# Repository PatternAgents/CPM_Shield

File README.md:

CPM Shield Adaptor
====================

PatternAgents CPM Shield Adaptor

[  
*PatternAgents CPM Shield Adaptor*](http://www.patternagents.com/projects/CPM_Shield.html)

The "CPM Shield Adaptor" board is designed to enable Cypress PSoC development boards to utilize Arduino Shield peripherals.

The PatternAgents "CPM Shield Adaptor" board supports :

Cypress CY8CKIT-001 : (Supports up to three (3) "CPM Shield Adaptor")

Cypress CY8CKIT-030 : (Supports up to two (2) "CPM Shield Adaptor")

Cypress CY8CKIT-050 : (Supports up to two (2) "CPM Shield Adaptor")

Cypress CY3280-28xxx : (Supports one (1) "CPM Shield Adaptor")

Cypress CY3280-22x45 : (Supports one (1) "CPM Shield Adaptor")

(Not an Exhaustive list as more Cypress development boards are routinely released)

For information on the Arduino Shield Specification, see http://www.arduino.cc

[  
*Licensing CC BY-NC-SA 4.0*](http://creativecommons.org/licenses/by-nc-sa/4.0/)

PatternAgents uses the increasingly popular business model called "Dual Licensing" 
in which both the open source software distribution mechanism and traditional commercial software distribution models are combined.

Open Source Projects:        

If you are developing and distributing open source applications under the Creative Commons CC BY-NC-SA 4.0, 
as published by the Creative Commons Foundation, then you are free to use the PatternAgents hardware/software under the CC BY-NC-SA 4.0 license. 
Please note that CC BY-NC-SA 4.0 requires that all modifications to the original code as well as all Derivative Works 
must also be released under the terms of the CC BY-NC-SA 4.0 license.

Closed Source Projects:

If you are developing and distributing traditional closed source or commercial applications, 
you must purchase a PatternAgents commercial use license, 
which is specifically designed for users interested in retaining the proprietary status of their designs and code. 
All PatternAgents commercial licenses expressly supersede the CC BY-NC-SA 4.0 license. 
This means that when you license the PatternAgents software under a commercial license, 
you specifically do not use the software under the CC BY-NC-SA 4.0 license and therefore you are not subject to any of its terms.
        
If you would like to use our designs for your own personal or educational use, have at it! 

Our public design repository is available at <a href="https://github.com/patternagents">Github</a>.

If you would like to produce our designs for commercial use, or as products for sale, 
please contact us to arrange for a Commercial Use license. We have many other designs, 
as well as options and extras that are not released publicly. 
We will also customize designs, firmware, and software for a reasonable fee, just contact us to discuss your requirements.

THIS SOFTWARE IS PROVIDED BY THE CONTRIBUTORS "AS IS" AND WITHOUT ANY EXPRESS OR IMPLIED WARRANTIES, 
INCLUDING, BUT NOT LIMITED TO, THE IMPLIED WARRANTIES OF MERCHANTABILITY AND FITNESS FOR A PARTICULAR PURPOSE ARE DISCLAIMED. 
IN NO EVENT SHALL THE COPYRIGHT OWNER OR CONTRIBUTORS BE LIABLE FOR ANY DIRECT, INDIRECT, INCIDENTAL, SPECIAL, EXEMPLARY, 
OR CONSEQUENTIAL DAMAGES (INCLUDING, BUT NOT LIMITED TO, PROCUREMENT OF SUBSTITUTE GOODS OR SERVICES; LOSS OF USE, DATA, 
OR PROFITS; OR BUSINESS INTERRUPTION) HOWEVER CAUSED AND ON ANY THEORY OF LIABILITY, WHETHER IN CONTRACT, 
STRICT LIABILITY, OR TORT (INCLUDING NEGLIGENCE OR OTHERWISE) ARISING IN ANY WAY OUT OF THE USE OF THIS SOFTWARE, 
EVEN IF ADVISED OF THE POSSIBILITY OF SUCH DAMAGE. 

-------------------------------------------------------------------------------------------

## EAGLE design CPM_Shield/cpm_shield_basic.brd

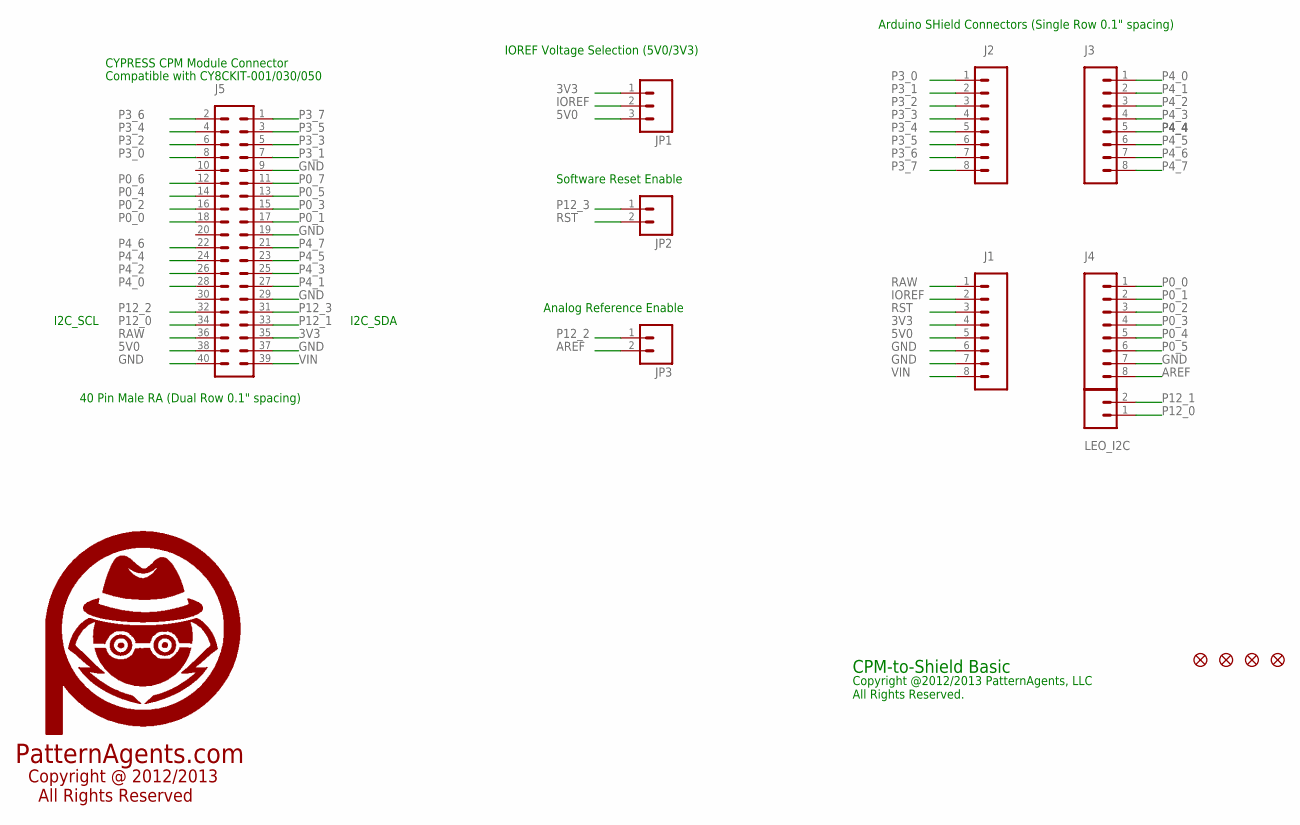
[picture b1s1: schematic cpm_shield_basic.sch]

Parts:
J1, J2, J3, J4: SAMTEC; 1X08
J5: SULLINS_SCS; MA20-2
JP1: M03PS; M03
JP2, JP3: M02PS; MA02
JP4, JP5, JP6, JP7: FIDUCIAL1.5X3; FIDUCIAL-1.5X3
LEO_I2C: M02PS; MA02
U$3: LOGO_PA_AGENTLARGE; LOGO_PA_AGENT_LARGE

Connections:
3V3: J1.4, J5.35, JP1.1
5V0: J1.5, J5.38, JP1.3
AREF: J4.8, JP3.2
GND: J1.6, J1.7, J4.7, J5.9, J5.19, J5.29, J5.37, J5.40
IOREF: J1.2, JP1.2
P0_0: J4.1, J5.18
P0_1: J4.2, J5.17
P0_2: J4.3, J5.16
P0_3: J4.4, J5.15
P0_4: J4.5, J5.14
P0_5: J4.6, J5.13
P0_6: J5.12
P0_7: J5.11
P3_0: J2.1, J5.8
P3_1: J2.2, J5.7
P3_2: J2.3, J5.6
P3_3: J2.4, J5.5
P3_4: J2.5, J5.4
P3_5: J2.6, J5.3
P3_6: J2.7, J5.2
P3_7: J2.8, J5.1
P4_0: J3.1, J5.28
P4_1: J3.2, J5.27
P4_2: J3.3, J5.26
P4_3: J3.4, J5.25
P4_4: J3.5, J5.24
P4_5: J3.6, J5.23
P4_6: J3.7, J5.22
P4_7: J3.8, J5.21
P12_0: J5.34, LEO_I2C.1
P12_1: J5.33, LEO_I2C.2
P12_2: J5.32, JP3.1
P12_3: J5.31, JP2.1
RAW: J1.1, J5.36
RST: J1.3, JP2.2
VIN: J1.8, J5.39

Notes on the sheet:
40 Pin Male RA (Dual Row 0.1" spacing)
CYPRESS CPM Module Connector
Compatible with CY8CKIT-001/030/050
Arduino SHield Connectors (Single Row 0.1" spacing)
I2C_SDA
I2C_SCL
IOREF Voltage Selection (5V0/3V3)
Software Reset Enable
Analog Reference Enable
CPM-to-Shield Basic
Copyright @2012/2013 PatternAgents, LLC All Rights Reserved.
PatternAgents.com
Copyright @ 2012/2013 All Rights Reserved

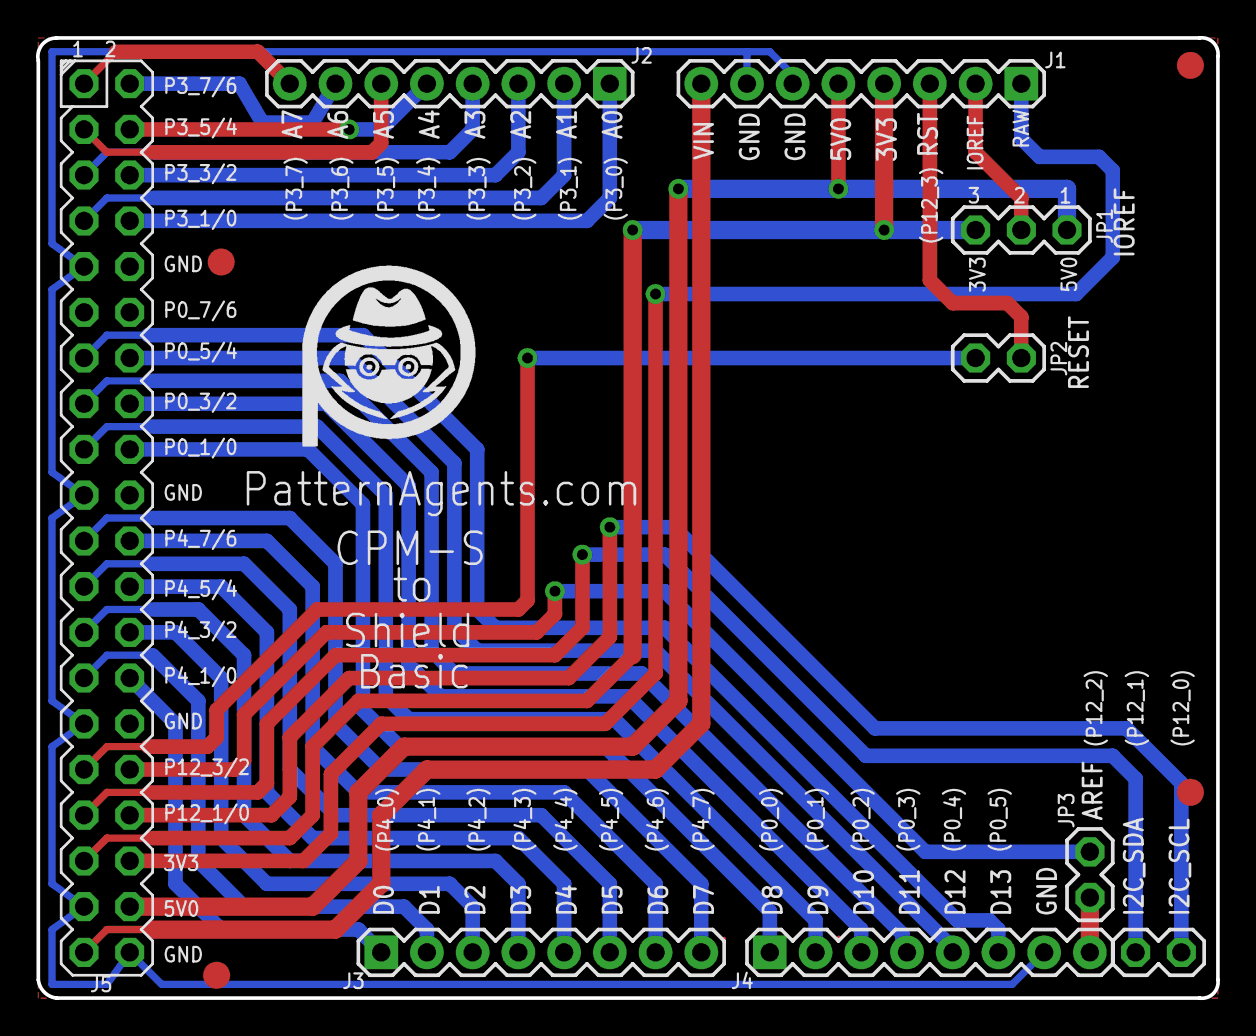
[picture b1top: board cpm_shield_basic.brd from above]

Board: 2 copper layers, 65.6 x 53.4 mm, 15 parts (1 on the bottom side), 34 nets.

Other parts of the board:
U$2: LOGO_PA_AGENT_LARGE

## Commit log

2013-07-17 initial project create
2013-07-18 add GPLv3/Dual license files
2013-07-18 add Eagle design files
2013-07-19 link fixes
2013-07-22 reduce png file sizes
2013-12-23 Move licensing to CC 4.0
